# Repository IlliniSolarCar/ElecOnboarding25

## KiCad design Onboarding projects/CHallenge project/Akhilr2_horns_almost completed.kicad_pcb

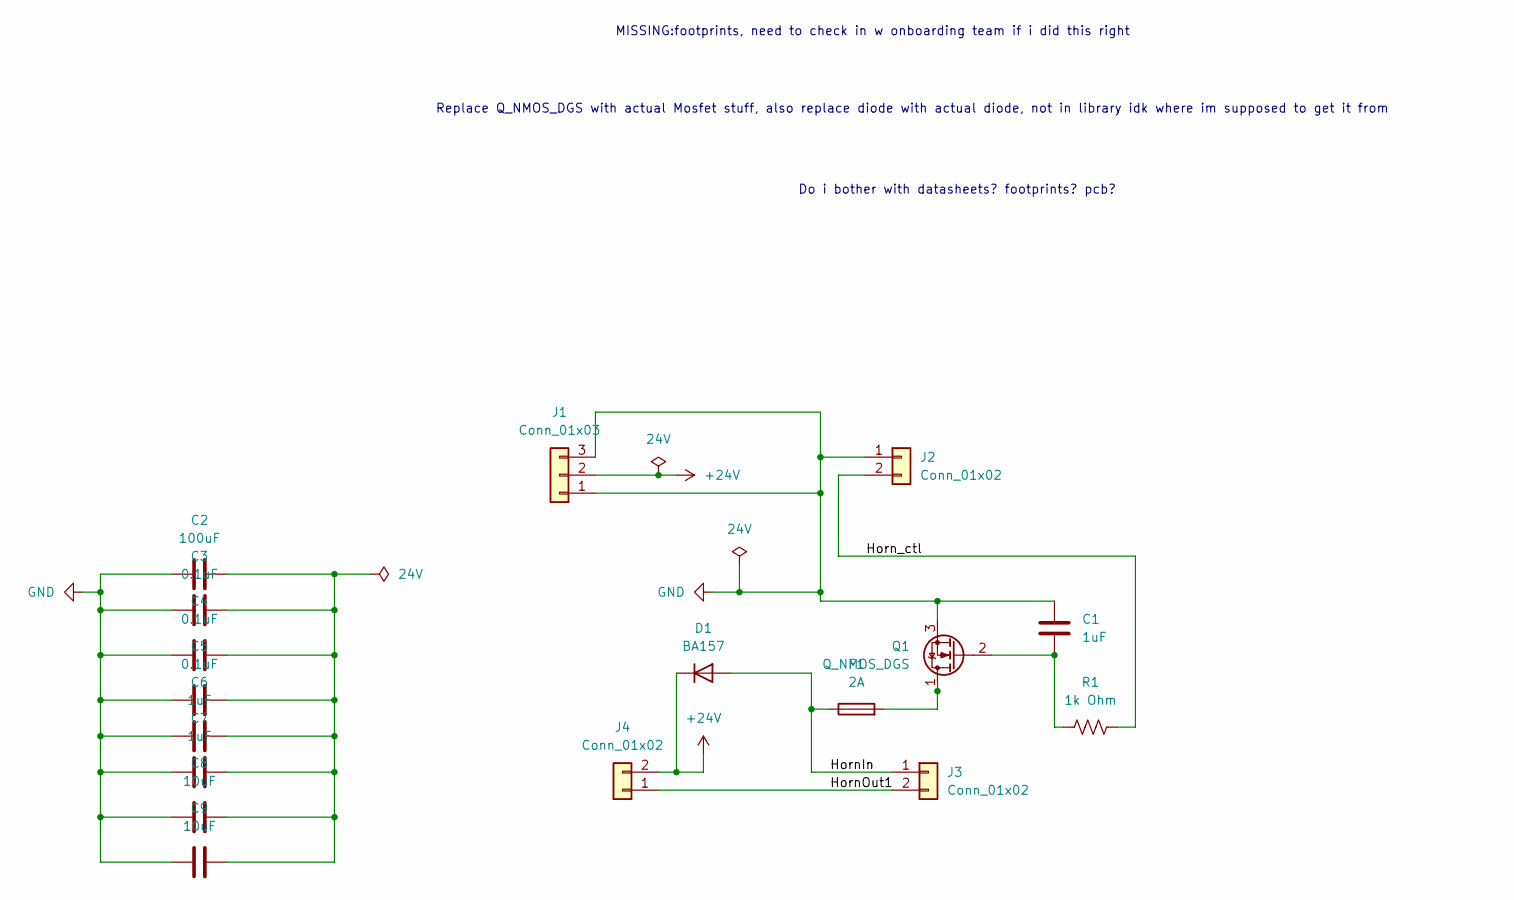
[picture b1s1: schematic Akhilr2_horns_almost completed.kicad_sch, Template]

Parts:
C1, C6, C7: 1uF
C2: 100uF
C3, C4, C5: 0.1uF
C8, C9: 10uF
D1: BA157; D_DO-41_SOD81_P10.16mm_Horizontal
F1: 2A
J1: Conn_01x03
J2, J3, J4: Conn_01x02
Q1: Q_NMOS_DGS; IRFR010PBF
R1: 1k Ohm

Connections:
+24V: D1.1 (K), J1.2, J4.2
/HornIn: D1.2 (A), F1.1, J3.1
/HornOut1: J3.2, J4.1
/Horn_ctl: J2.2, R1.2
GND: C1.2, C2.1, C3.1, C4.1, C5.1, C6.1, C7.1, C8.1, C9.1, J1.1, J1.3, J2.1, Q1.3 (S)
unnamed: C2.2, C3.2, C4.2, C5.2, C6.2, C7.2, C8.2, C9.2
unnamed: F1.2, Q1.1 (D)
unnamed: C1.1, Q1.2 (G), R1.1

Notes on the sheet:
Replace Q_NMOS_DGS with actual Mosfet stuff, also replace diode with actual diode, not in library idk where im supposed to get it from
MISSING:footprints, need to check in w onboarding team if i did this right
Do i bother with datasheets? footprints? pcb?

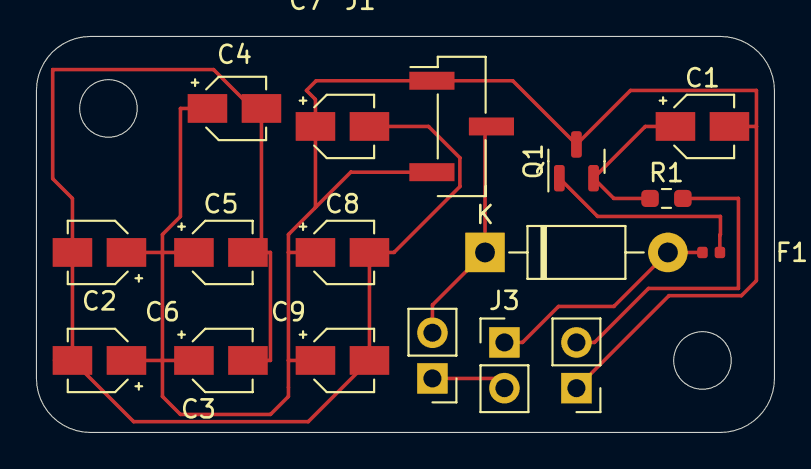
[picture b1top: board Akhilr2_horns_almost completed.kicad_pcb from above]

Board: 2 copper layers, 41.0 x 22.0 mm, 17 parts (0 on the bottom side), 8 nets.

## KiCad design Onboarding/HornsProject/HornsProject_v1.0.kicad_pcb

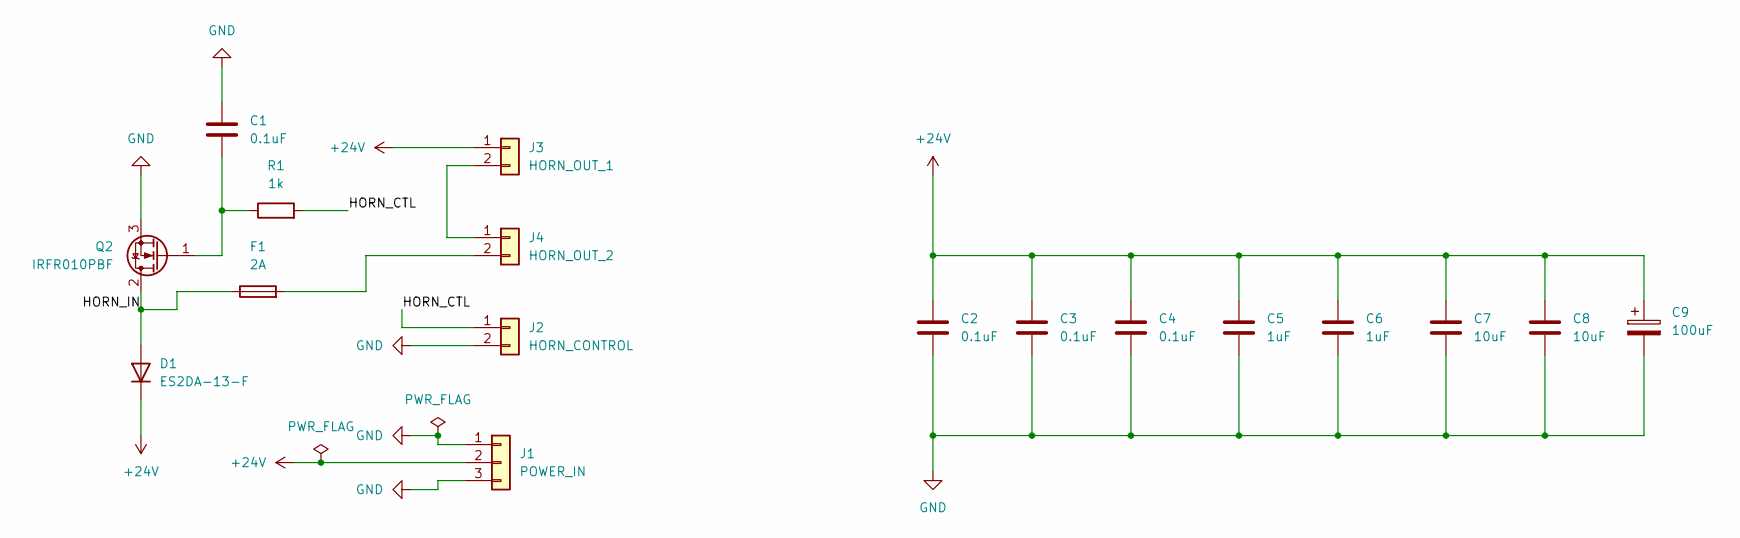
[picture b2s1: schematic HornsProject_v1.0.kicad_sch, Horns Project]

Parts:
C1, C2, C3, C4: 0.1uF; C_0805_2012Metric_Pad1.18x1.45mm_HandSolder
C5, C6: 1uF; C_0805_2012Metric_Pad1.18x1.45mm_HandSolder
C7, C8: 10uF; C_1206_3216Metric_Pad1.33x1.80mm_HandSolder
C9: 100uF; CP_Radial_D6.3mm_P2.50mm
D1: ES2DA-13-F; D_SMA
F1: 2A; Fuse_1206_3216Metric_Pad1.42x1.75mm_HandSolder
J1: POWER_IN; Molex_KK-254_AE-6410-03A_1x03_P2.54mm_Vertical
J2: HORN_CONTROL; Molex_KK-254_AE-6410-02A_1x02_P2.54mm_Vertical
J3: HORN_OUT_1; Molex_KK-254_AE-6410-02A_1x02_P2.54mm_Vertical
J4: HORN_OUT_2; Molex_KK-254_AE-6410-02A_1x02_P2.54mm_Vertical
Q2: IRFR010PBF; TO-252-2
R1: 1k; R_0805_2012Metric_Pad1.20x1.40mm_HandSolder

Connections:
+24V: C2.1, C3.1, C4.1, C5.1, C6.1, C7.1, C8.1, C9.1, D1.1 (K), J1.2, J3.1
/HORN_CTL: J2.1, R1.2
/HORN_IN: D1.2 (A), F1.1, Q2.2 (D)
GND: C1.2, C2.2, C3.2, C4.2, C5.2, C6.2, C7.2, C8.2, C9.2, J1.1, J1.3, J2.2, Q2.3 (S)
unnamed: J3.2, J4.1
unnamed: F1.2, J4.2
unnamed: C1.1, Q2.1 (G), R1.1

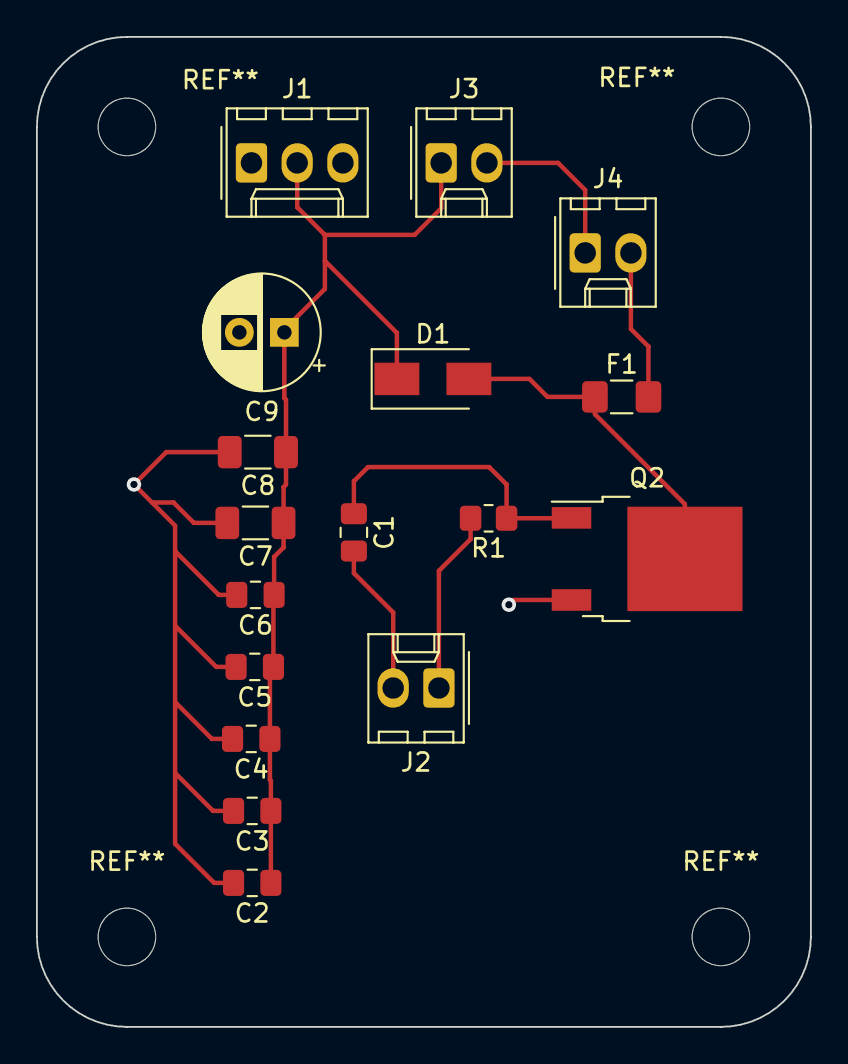
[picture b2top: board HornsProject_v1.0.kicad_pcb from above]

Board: 2 copper layers, 43.0 x 55.0 mm, 17 parts (0 on the bottom side), 7 nets.

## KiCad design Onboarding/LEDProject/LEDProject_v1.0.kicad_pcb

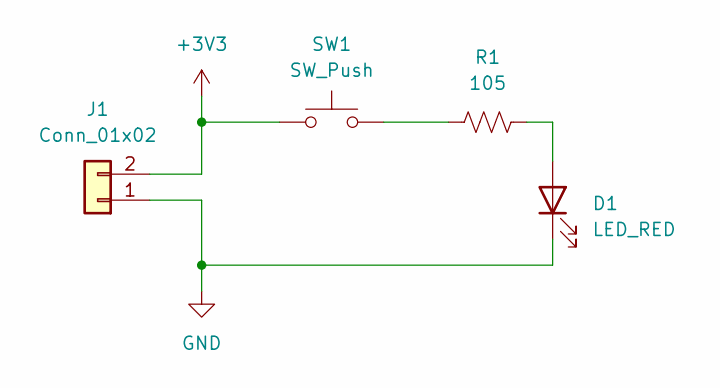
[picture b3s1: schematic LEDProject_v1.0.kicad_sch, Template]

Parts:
D1: LED_RED; LED_0603_Symbol_on_F.SilkS
J1: Conn_01x02; Molex_KK-254_AE-6410-02A_1x02_P2.54mm_Vertical; MPN 022272021
R1: 105; R_0603_1608Metric_Pad0.98x0.95mm_HandSolder
SW1: SW_Push; SW_DIP_SPSTx01_Slide_6.7x4.1mm_W8.61mm_P2.54mm_LowProfile; MPN 1825910-6

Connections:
+3V3: J1.2, SW1.1
GND: D1.1 (K), J1.1
unnamed: D1.2 (A), R1.2
unnamed: R1.1, SW1.2

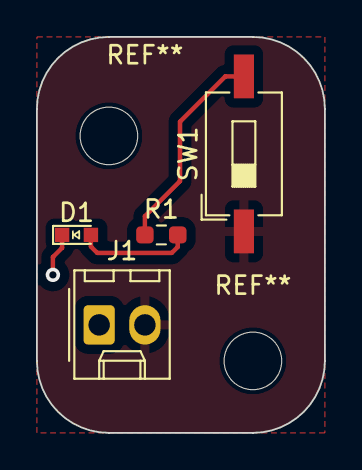
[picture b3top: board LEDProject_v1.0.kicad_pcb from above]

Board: 2 copper layers, 16.0 x 22.0 mm, 4 parts (0 on the bottom side), 4 nets.

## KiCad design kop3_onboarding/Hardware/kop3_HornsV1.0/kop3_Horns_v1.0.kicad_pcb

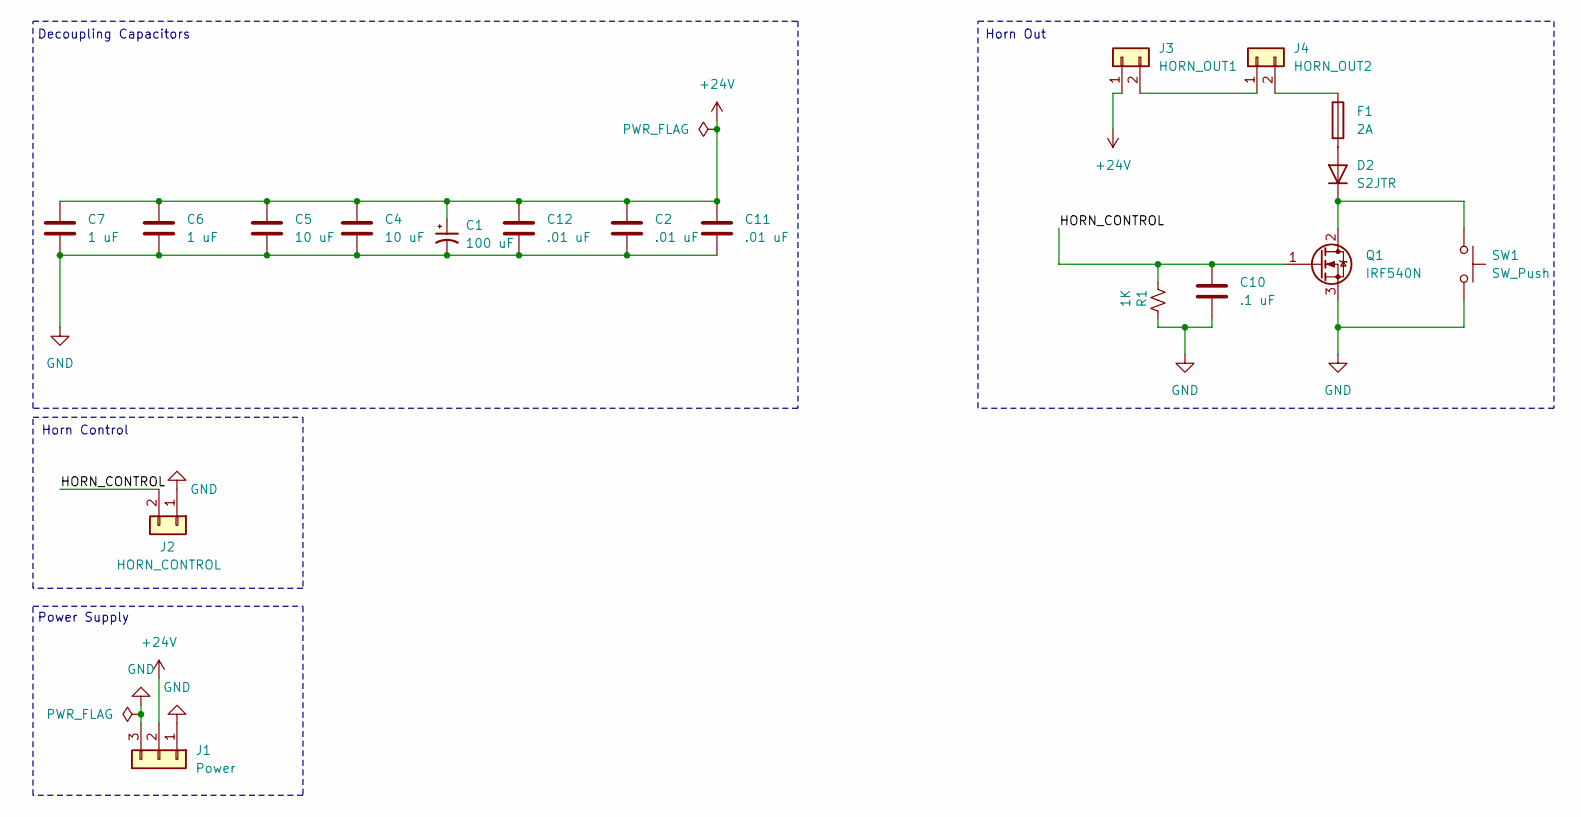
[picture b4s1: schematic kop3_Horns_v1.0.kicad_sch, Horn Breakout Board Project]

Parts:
C1: 100 uF; C_0805_2012Metric_Pad1.18x1.45mm_HandSolder
C2, C11, C12: .01 uF; C_0805_2012Metric_Pad1.18x1.45mm_HandSolder
C4, C5: 10 uF; C_0805_2012Metric_Pad1.18x1.45mm_HandSolder
C6, C7: 1 uF; C_0805_2012Metric_Pad1.18x1.45mm_HandSolder
C10: .1 uF; C_0805_2012Metric_Pad1.18x1.45mm_HandSolder
D2: S2JTR; D_SMB
F1: 2A; Fuse_0805_2012Metric_Pad1.15x1.40mm_HandSolder
J1: Power; Molex_KK-254_AE-6410-03A_1x03_P2.54mm_Vertical
J2: HORN_CONTROL; Molex_KK-254_AE-6410-02A_1x02_P2.54mm_Vertical
J3: HORN_OUT1; Molex_KK-254_AE-6410-02A_1x02_P2.54mm_Vertical
J4: HORN_OUT2; Molex_KK-254_AE-6410-02A_1x02_P2.54mm_Vertical
Q1: IRF540N; TO-220-3_Vertical
R1: 1K; R_Axial_DIN0204_L3.6mm_D1.6mm_P5.08mm_Horizontal
SW1: SW_Push; SW_Push_1P1T_NO_6x6mm_H9.5mm

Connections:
+24V: C1.1, C2.1, C4.1, C5.1, C6.1, C7.1, C11.1, C12.1, J1.2, J3.1
/HORN_CONTROL: C10.1, J2.2, Q1.1 (G), R1.2
GND: C1.2, C2.2, C4.2, C5.2, C6.2, C7.2, C10.2, C11.2, C12.2, J1.1, J1.3, J2.1, Q1.3 (S), R1.1, SW1.2
unnamed: D2.2 (A), F1.2
unnamed: D2.1 (K), Q1.2 (D), SW1.1
unnamed: J3.2, J4.1
unnamed: F1.1, J4.2

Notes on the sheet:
Power Supply
Horn Control
Horn Out
Decoupling Capacitors

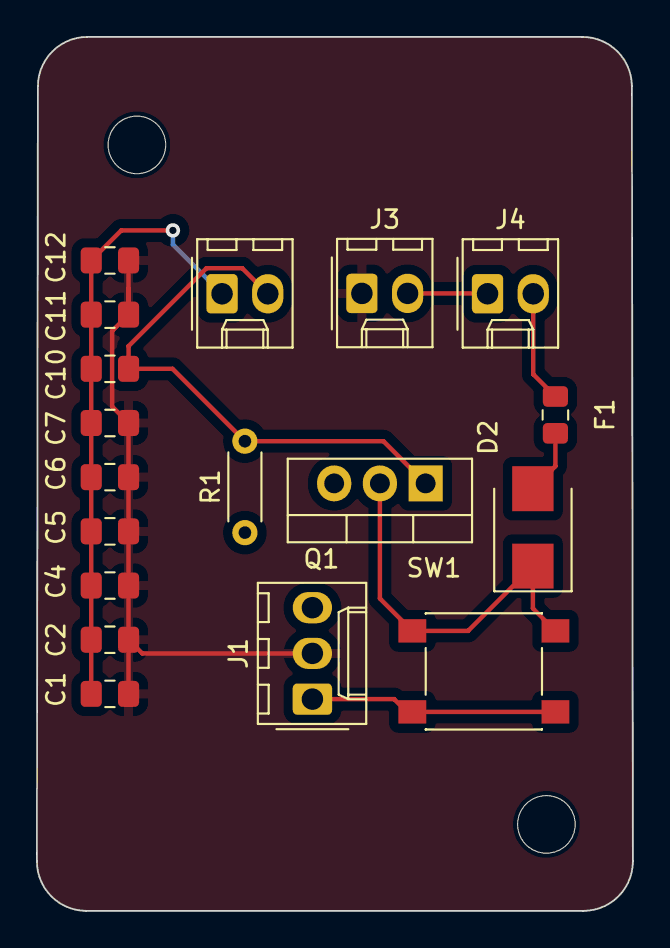
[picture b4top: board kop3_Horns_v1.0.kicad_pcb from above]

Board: 2 copper layers, 33.1 x 48.6 mm, 18 parts (0 on the bottom side), 7 nets.

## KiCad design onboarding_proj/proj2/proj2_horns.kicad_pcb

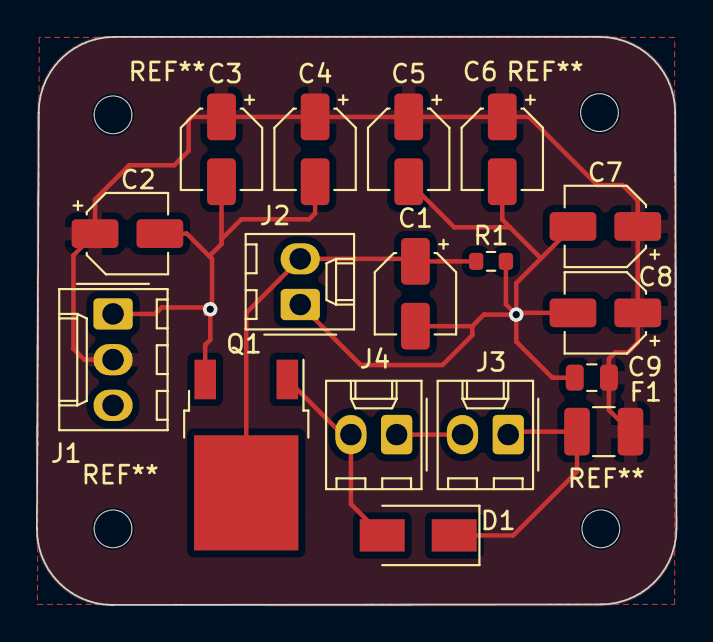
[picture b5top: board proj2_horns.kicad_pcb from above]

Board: 2 copper layers, 35.5 x 31.6 mm, 17 parts (0 on the bottom side), 6 nets.

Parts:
C1, C2, C3, C4: 0.1uF; CP_Elec_4x4.5
C5, C6: 1uF; CP_Elec_4x4.5
C7, C8: 10uF; CP_Elec_4x4.5
C9: 100uF; C_0805_2012Metric
D1: ES2DA-13-F; D_SMA
F1: 2A; Fuse_1210_3225Metric_Pad1.42x2.65mm_HandSolder
J1: Conn_01x03; Molex_KK-254_AE-6410-03A_1x03_P2.54mm_Vertical
J2, J3, J4: Conn_01x02; Molex_KK-254_AE-6410-02A_1x02_P2.54mm_Vertical
Q1: IRFR010PBF; TO-252-2
R1: 1000; R_0603_1608Metric

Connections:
+24V: C2.1, C3.1, C4.1, C5.1, C6.1, C7.1, C8.1, C9.1, F1.1, J1.2
GND: C1.2, C2.2, C3.2, C4.2, C5.2, C6.2, C7.2, C8.2, C9.2, J1.1, J1.3, J2.1, Q1.3 (S), R1.2
unnamed: D1.2 (A), J4.2, Q1.1 (D)
unnamed: D1.1 (K), F1.2, J3.1
unnamed: C1.1, J2.2, Q1.2 (G), R1.1
unnamed: J3.2, J4.1
